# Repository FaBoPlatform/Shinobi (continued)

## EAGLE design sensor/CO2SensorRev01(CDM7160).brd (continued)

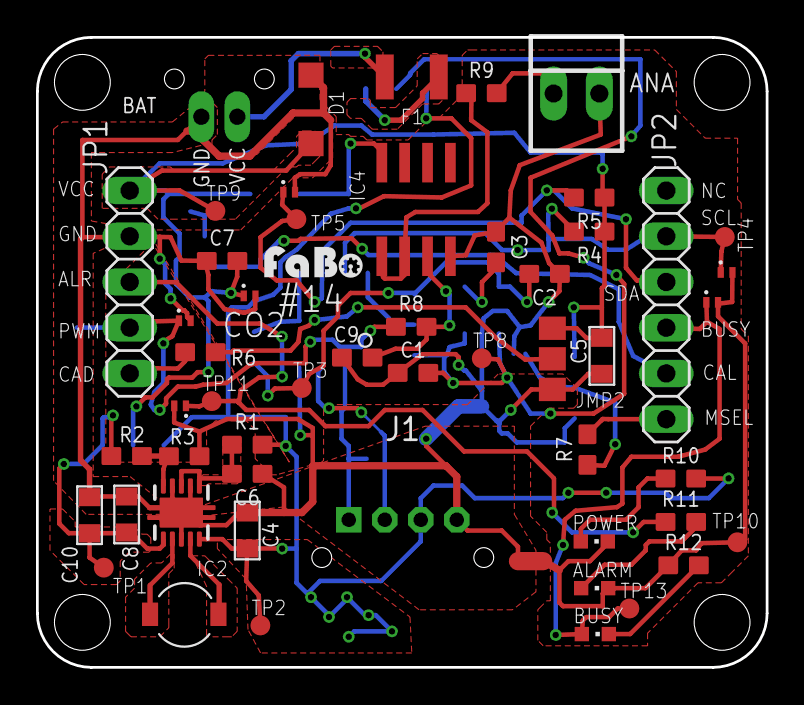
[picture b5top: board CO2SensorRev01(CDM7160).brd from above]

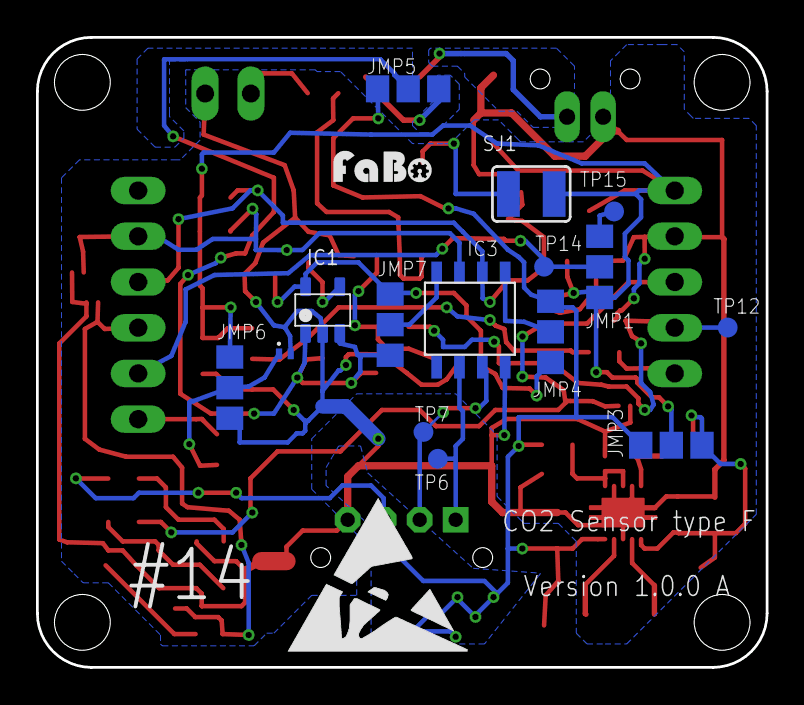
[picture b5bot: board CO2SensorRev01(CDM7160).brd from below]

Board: 2 copper layers, 40.5 x 35.0 mm, 71 parts (17 on the bottom side), 35 nets.

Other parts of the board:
U$2: FABO-SHINOBI
U$5: ESD_10.00
U$6, U$10: LOGO_FABO_S

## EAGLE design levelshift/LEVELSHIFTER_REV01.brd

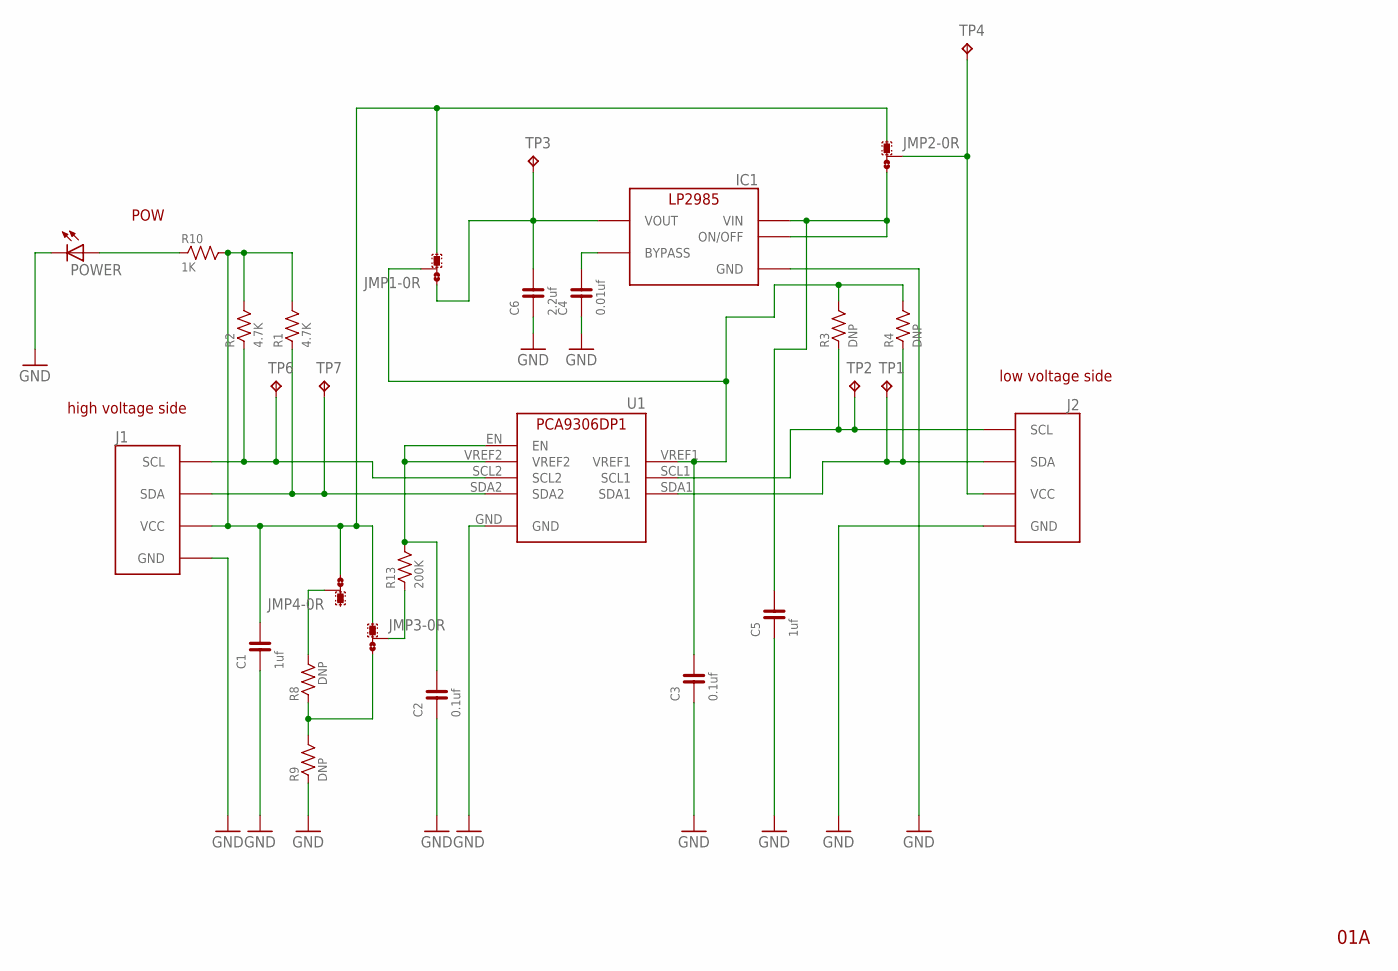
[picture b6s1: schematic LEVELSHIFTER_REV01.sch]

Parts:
C1, C5: 1uf; 0603
C2, C3: 0.1uf; 0603
C4: 0.01uf; 0603
C6: 2.2uf; 0603
IC1: LP2985-33DBV; SOT-23-5
J1, J2: FABO_BRICK_I2C-S04B-PASK-2; FABO_BRICK_I2C_S04B-PASK-2
JMP1, JMP2, JMP3, JMP4: 0R-JUMPA; A0R-JMP
POWER: LEDCHIPLED_0603; CHIPLED_0603
R1, R2: 4.7K; 0603
R3, R4, R8, R9: DNP; 0603
R10: 1K; 0603
R13: 200K; 0603
TP1, TP2, TP3, TP4, TP6, TP7: TPTP11R; TP11R
U1: PCA9306DP1; TSSOP8

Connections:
GND: C1.1, C2.1, C3.1, C4.1, C5.1, C6.1, IC1.2 (GND), J1.GND, J2.GND, POWER.C, R9.1, U1.GND
unnamed: J1.SDA, R1.1, TP7.TP, U1.SDA2
unnamed: J1.SCL, R2.1, TP6.TP, U1.SCL2
unnamed: C2.2, R13.2, U1.EN, U1.VREF2
unnamed: JMP3.3, R8.1, R9.2
unnamed: J2.SCL, R3.1, TP2.TP, U1.SCL1
unnamed: J2.SDA, R4.1, TP1.TP, U1.SDA1
unnamed: C3.2, JMP1.2, R3.2, R4.2, U1.VREF1
unnamed: C5.2, IC1.1 (VIN), IC1.3 (ON/OFF), JMP2.3
unnamed: JMP4.2, R8.2
unnamed: C6.2, IC1.5 (VOUT), JMP1.1, TP3.TP
unnamed: JMP3.2, R13.1
unnamed: C4.2, IC1.4 (BYPASS)
unnamed: J2.VCC, JMP2.2, TP4.TP
unnamed: POWER.A, R10.1
VCC: C1.2, J1.VCC, JMP1.3, JMP2.1, JMP3.1, JMP4.3, R1.2, R2.2, R10.2

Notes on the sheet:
01A
POW
high voltage side
low voltage side

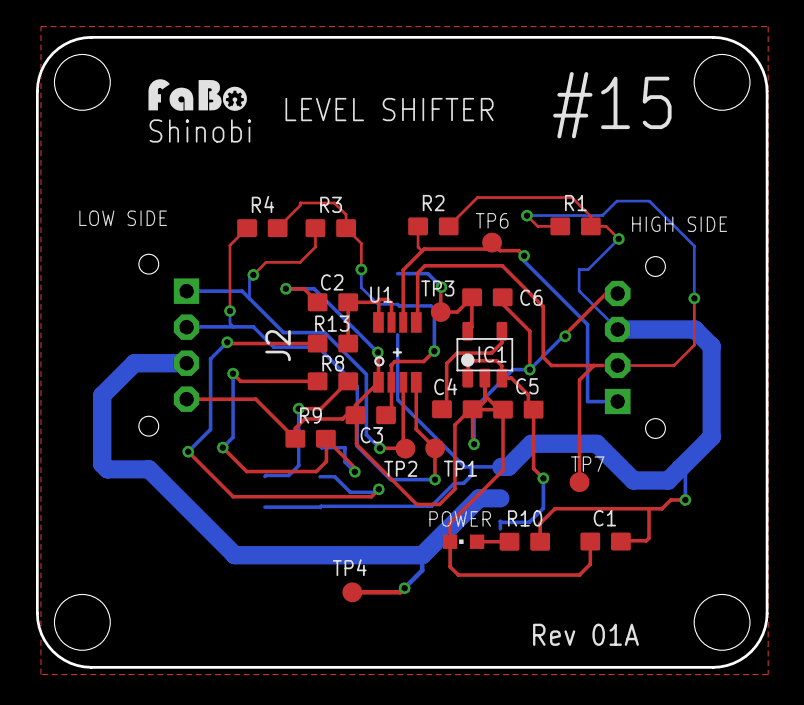
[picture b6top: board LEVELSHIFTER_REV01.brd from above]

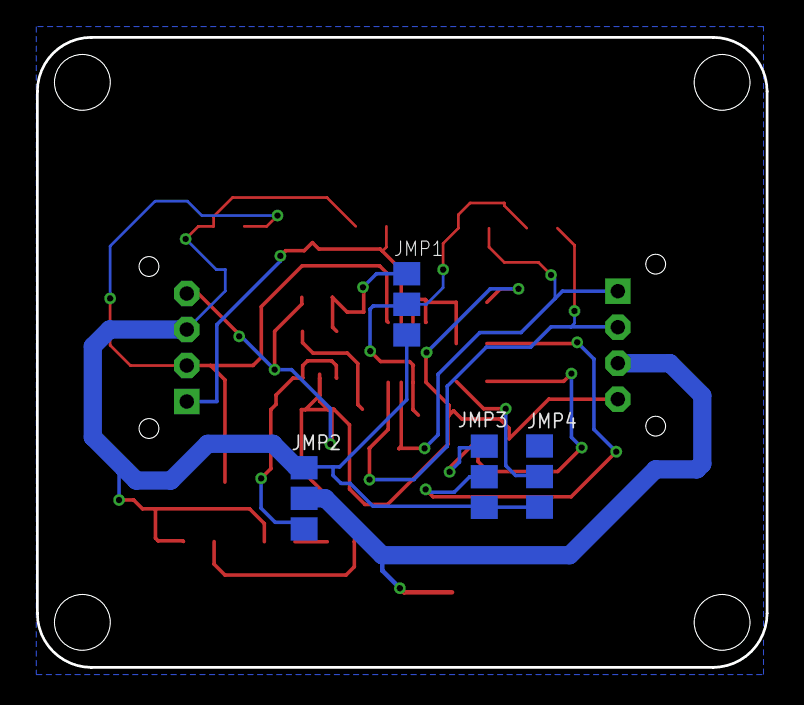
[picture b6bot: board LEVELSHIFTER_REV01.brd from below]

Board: 2 copper layers, 40.5 x 35.0 mm, 31 parts (4 on the bottom side), 16 nets.

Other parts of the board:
U$1: LOGO_FABO_S
U$2: FABO-SHINOBI

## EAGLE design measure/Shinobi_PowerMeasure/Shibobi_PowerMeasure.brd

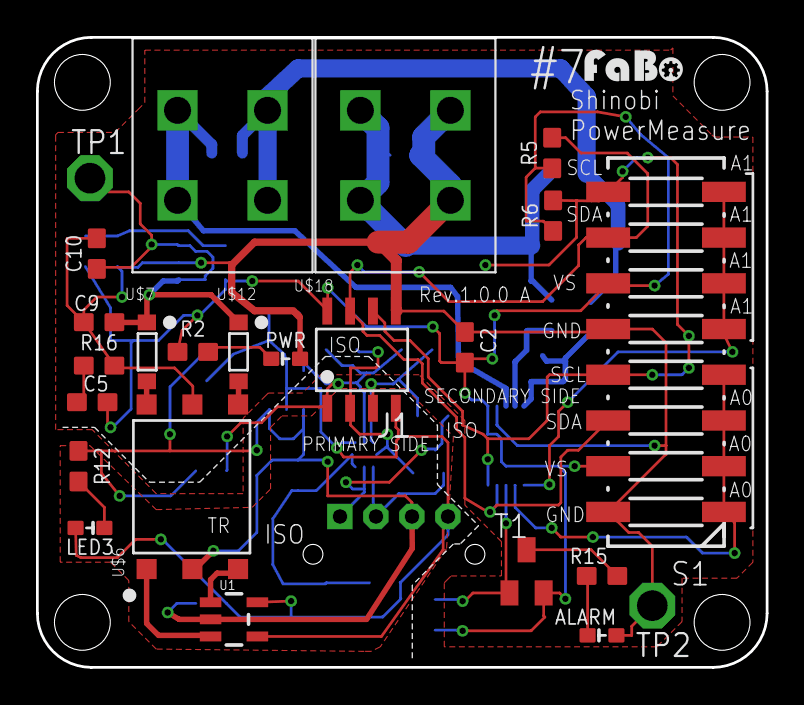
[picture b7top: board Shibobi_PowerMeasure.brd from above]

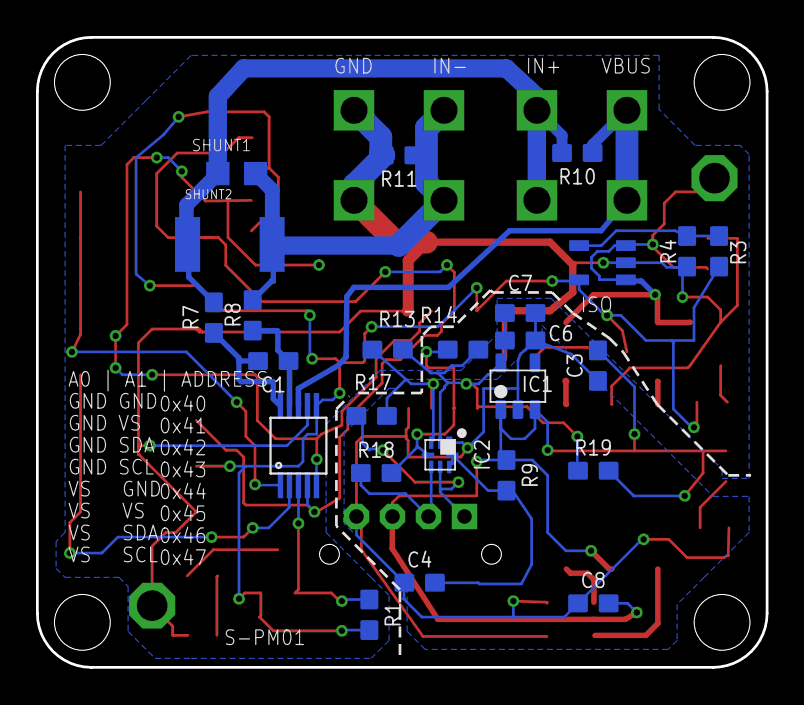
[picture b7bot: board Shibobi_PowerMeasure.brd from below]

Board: 2 copper layers, 40.5 x 35.0 mm, 52 parts (25 on the bottom side), 31 nets.

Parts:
ALARM: RED; 0603
C1, C2, C3, C4, C10: 0.1uF; 0603
C5, C8, C9: 10uF; 0603
C6: 1uF; 0603
C7: NC; 0603
IC1: 3.3V; SOT-23-5
IC2: XQFN8
J1: FABO_BRICK_I2C_S04B-PASK-2
LED3: BLUE; 0603
PWR: GREEN; 0603
R1, R5, R6, R13, R14: 4.7KΩ; 0603
R2, R12: 1KΩ; 0603
R3: 300K; 0603
R4: 150K; 0603
R7, R8: 10Ω; 0603
R9: 200KΩ; 0603
R10: 0Ω; 0603
R11: DNP; 0603
R15: 510Ω; 0603
R16: 1Ω; 0603
R17, R18, R19: NC; 0603
S1: 219-08J; CTS-219-08J
SHUNT1: PMR10EZPFV2L00
SHUNT2: WSL2010R0250FEB
T1: SC59-BEC
TP1, TP2: TPPAD1-17; P1-17
U1: SN6501DBVR; SOT-23-5
U2: TI-INA226
U$2, U$3: ML-1400-S1
U$5: FABO-SHINOBI
U$6: 760390014
U$7, U$12: MBR0520L; MBR0502L
U$8: TPS76333
U$18: ISO1541
U$19: LOGO_FABO_S

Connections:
3.3V: C2.2, C5.2, R1.2, R2.1, R3.2, R5.1, R6.1, S1.11, S1.15, T1.E, U2.6, U$8.OUT, U$18.VCC2
A0: S1.1, S1.2, S1.3, S1.4, U2.2
A1: S1.5, S1.6, S1.7, S1.8, U2.1
GND: C3.1, C4.1, C6.2, C7.2, C8.1, IC1.2, IC2.1, J1.GND, LED3.CATHODE, U1.4, U1.5, U$18.GND1
GND_SECONDARY: ALARM.CATHODE, C2.1, C9.2, C10.2, PWR.CATHODE, R4.2, R11.2, R16.2, S1.12, S1.16, TP2.TP, U2.7, U$3.RIGHT1, U$3.RIGHT2, U$6.5, U$8.GND, U$18.GND2
unnamed: C1.2, R7.1, U2.10
unnamed: C1.1, R8.1, U2.9
unnamed: U1.3, U$6.1
unnamed: U1.1, U$6.3
unnamed: R1.1, T1.B, U2.3
unnamed: U$6.6, U$7.P$2
unnamed: ALARM.ANODE, R15.1
unnamed: PWR.ANODE, R2.2
unnamed: R15.2, T1.C
unnamed: LED3.ANODE, R12.2
unnamed: IC2.4, R14.1, R18.2, U$18.SDA1
unnamed: IC2.6, J1.SCL, R17.1
unnamed: C6.1, C7.1, IC1.5, IC2.2, R13.2, R14.2, R19.1, U$18.VCC1
unnamed: U$6.4, U$12.P$2
unnamed: C9.1, C10.1, TP1.TP, U$7.P$1, U$8.EN, U$8.IN, U$12.P$1
unnamed: C4.2, IC2.7, IC2.8, R9.2
unnamed: C3.2, C8.2, IC1.1, IC1.3, J1.VCC, R9.1, R12.1, R19.2, U1.2, U$6.2
unnamed: R3.1, R4.1, U$8.NC/FB
unnamed: C5.1, R16.1
unnamed: IC2.5, J1.SDA, R18.1
unnamed: IC2.3, R13.1, R17.2, U$18.SCL1
SCL: R6.2, S1.9, S1.13, U2.5, U$18.SCL2
SDA: R5.2, S1.10, S1.14, U2.4, U$18.SDA2
VBUS: R10.1, U2.8, U$2.LEFT1, U$2.LEFT2
VIN+: R7.2, R10.2, SHUNT1.P$2, SHUNT2.P$2, U$2.RIGHT1, U$2.RIGHT2
VIN-: R8.2, R11.1, SHUNT1.P$1, SHUNT2.P$1, U$3.LEFT1, U$3.LEFT2

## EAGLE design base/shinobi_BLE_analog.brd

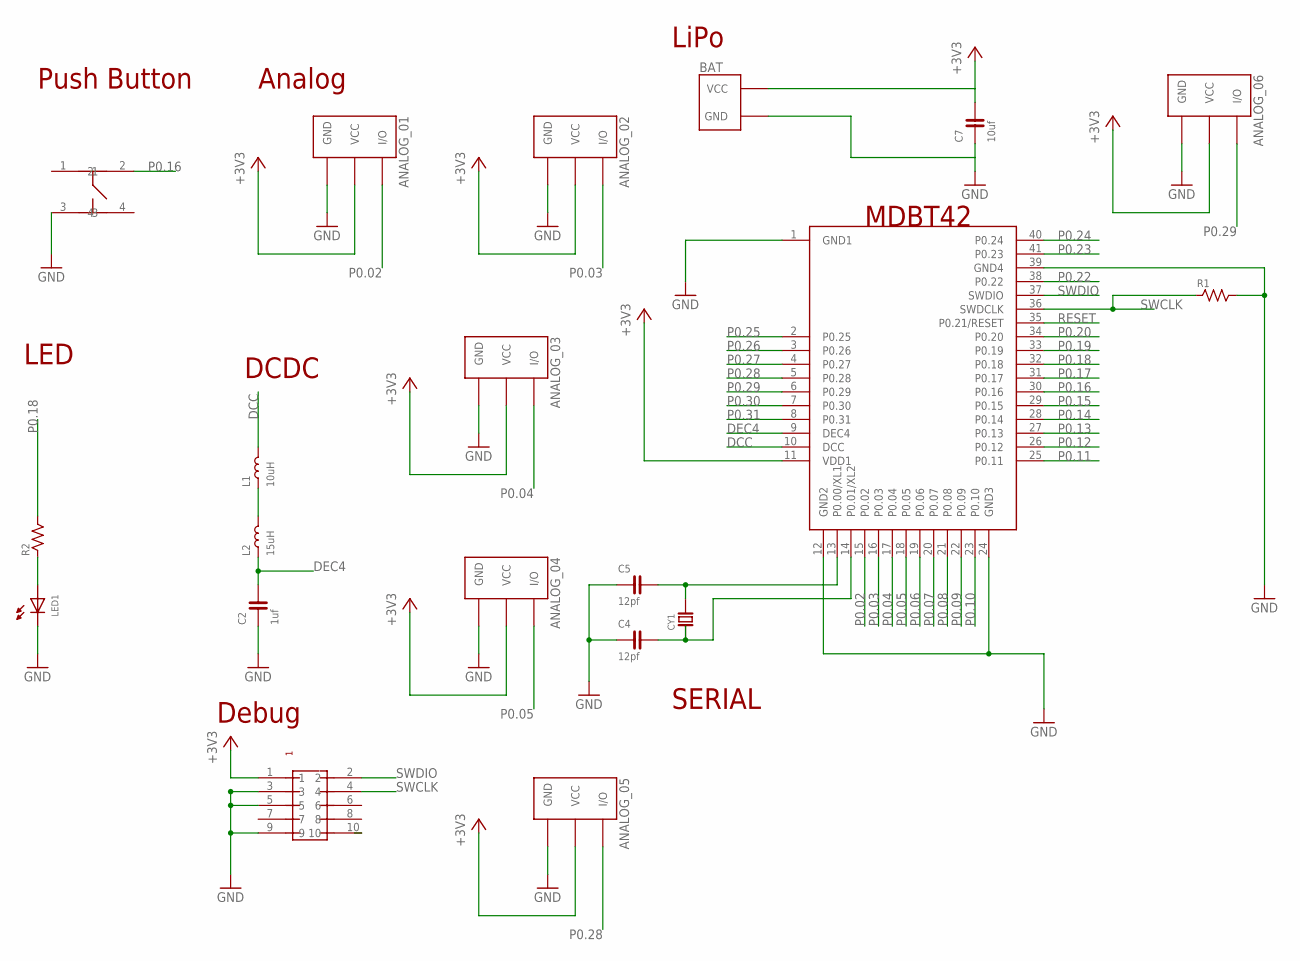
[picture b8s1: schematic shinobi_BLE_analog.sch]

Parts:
ANALOG_01, ANALOG_02, ANALOG_03, ANALOG_04, ANALOG_05, ANALOG_06: FABO_BRICK_3PIN-S03B-PASK-2_LONG; FABO_BRICK_3PIN_S03B-PASK-2_LONG
BAT: FABO_BRICK_2PIN_SIDE; FABO_BRICK_2PIN_S02B−PASK-2_SILK
C2: 1uf; 0603
C4, C5: 12pf; 0603
C7: 10uf; 0603
CY1: CRYSTAL-ABS07; ABRACON-ABS07-32.768KHZ
L1: 10uH; 0603
L2: 15uH; 1812
LED1: LED-0603; 0603
R1, R2: RESISTOR-0603; 0603
U$2: RAYTAC-MDBT42
U$4: PIN-HEADER-SMT(1.27MM)2X5
U$5: SWICTH-4P(KMR2); SWITCH-4P(KMR2)

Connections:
+3V3: ANALOG_01.VCC, ANALOG_02.VCC, ANALOG_03.VCC, ANALOG_04.VCC, ANALOG_05.VCC, ANALOG_06.VCC, BAT.VCC, C7.2, U$2.11 (VDD1), U$4.1
DCC: L1.2, U$2.10 (DCC)
DEC4: C2.2, L2.P$1 (1), U$2.9 (DEC4)
GND: ANALOG_01.GND, ANALOG_02.GND, ANALOG_03.GND, ANALOG_04.GND, ANALOG_05.GND, ANALOG_06.GND, BAT.GND, C2.1, C4.1, C5.1, C7.1, LED1.CATHODE, R1.2, U$2.1 (GND1), U$2.12 (GND2), U$2.24 (GND3), U$2.39 (GND4), U$4.3, U$4.5, U$4.9, U$5.3
unnamed: LED1.ANODE, R2.1
unnamed: L1.1, L2.P$2 (2)
unnamed: C5.2, CY1.P$2, U$2.13 (P0.00/XL1)
unnamed: C4.2, CY1.P$1, U$2.14 (P0.01/XL2)
P0.02: ANALOG_01.I/O, U$2.15 (P0.02)
P0.03: ANALOG_02.I/O, U$2.16 (P0.03)
P0.04: ANALOG_03.I/O, U$2.17 (P0.04)
P0.05: ANALOG_04.I/O, U$2.18 (P0.05)
P0.06: U$2.19 (P0.06)
P0.07: U$2.20 (P0.07)
P0.08: U$2.21 (P0.08)
P0.09: U$2.22 (P0.09)
P0.10: U$2.23 (P0.10)
P0.11: U$2.25 (P0.11)
P0.12: U$2.26 (P0.12)
P0.13: U$2.27 (P0.13)
P0.14: U$2.28 (P0.14)
P0.15: U$2.29 (P0.15)
P0.16: U$2.30 (P0.16), U$5.2
P0.17: U$2.31 (P0.17)
P0.18: R2.2, U$2.32 (P0.18)
P0.19: U$2.33 (P0.19)
P0.20: U$2.34 (P0.20)
P0.22: U$2.38 (P0.22)
P0.23: U$2.41 (P0.23)
P0.24: U$2.40 (P0.24)
P0.25: U$2.2 (P0.25)
P0.26: U$2.3 (P0.26)
P0.27: U$2.4 (P0.27)
P0.28: ANALOG_05.I/O, U$2.5 (P0.28)
P0.29: ANALOG_06.I/O, U$2.6 (P0.29)
P0.30: U$2.7 (P0.30)
P0.31: U$2.8 (P0.31)
RESET: U$2.35 (P0.21/RESET)
RESET1: U$4.10
SWCLK: R1.1, U$2.36 (SWDCLK), U$4.4
SWDIO: U$2.37 (SWDIO), U$4.2

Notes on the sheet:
Push Button
MDBT42
LED
Debug
DCDC
SERIAL
Analog
LiPo

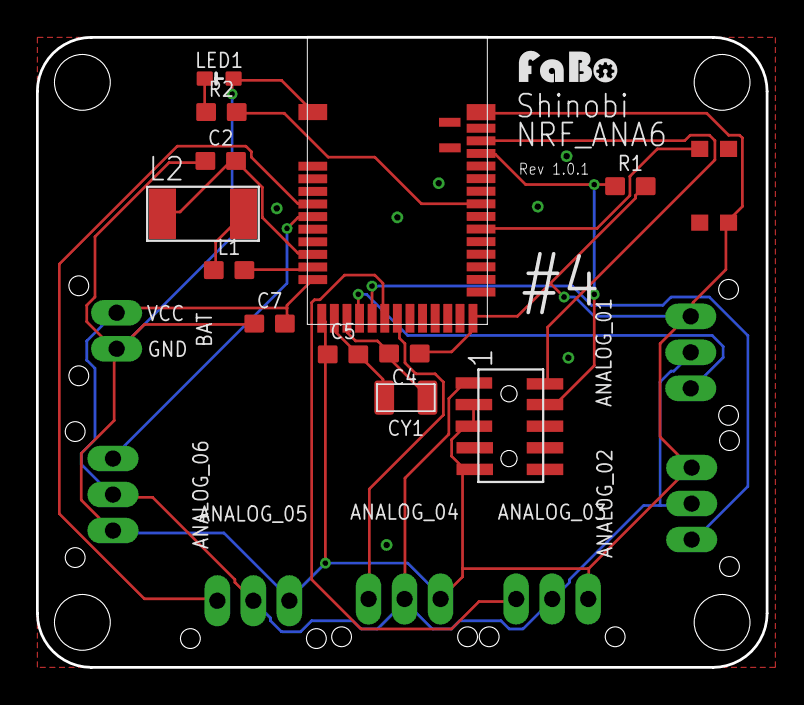
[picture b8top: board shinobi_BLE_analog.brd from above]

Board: 2 copper layers, 40.5 x 35.0 mm, 22 parts (0 on the bottom side), 18 nets.

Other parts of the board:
U$1: FABO-SHINOBI
U$3: LOGO_FABO_S

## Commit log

2017-12-25 Initial commit.
2017-12-25 Add TPS63000 module.
2017-12-25 Update.
2017-12-26 Update 3v3.
2018-01-19 Update Shinobi.
2018-04-04 Solar Add resistance constant,PowerMeasure
2018-05-10 Dimention Delete
2018-06-06 Add silk printing Fixed garbled characters
2018-07-05 R4,R3 regstance exchnage.add info
2019-03-12 Update gitignore.
2019-03-12 Update BLE with connector.
2019-03-15 LEVEL SHIFT NEW RELESE ADDTION.
2019-03-16 Add connector version
2019-03-22 CDM7160-C00 Addtion.
2019-04-25 Add shinobi connector.
2020-07-09 シルク削除
2020-07-09 #21 Shinobi Enviroment 1.0.1 アップデート VCC ５V対応 LDO、レベル変換、BME６８０通風口追加、番号の変更 ４から２１
2020-07-10 ファイル削除
2020-07-26 #17 PWM 番号変更とピンを１６本化
2022-10-18 #1 Shinobi NRFBASE アップデート アンテナ下部ベタ見直し、電源コネクタ強度をアップ
2022-10-22 #1 Shinobi NRF Rev010001 オーバーラップ修正

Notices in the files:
parts and their libraries:
FaBo-Inductor: Released under the Creative Commons Attribution-ShareAlike 4.0 License
https://creativecommons.org/licenses/by-sa/4.0
gclue: Released under the Creative Commons
SparkFun: Licensing: CC v3.0 Share-Alike You are welcome to use this library for commercial purposes.
